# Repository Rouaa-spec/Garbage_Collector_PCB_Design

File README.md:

# [Hardware Design] Carte Électronique de Contrôle — Robot Autonome Tri-Canettes

Ce dépôt rassemble les fichiers de conception matérielle de la carte de contrôle dédiée à un robot autonome de collecte et de tri de déchets. 

La carte centralise la gestion de l'alimentation (Li-Ion), le pilotage des moteurs DC et l'acquisition des capteurs de navigation sur bus partagés.

📌 **Statut du projet :** 
* 🟧 **Routage PCB (KiCad) :** En cours de réalisation...

---

## 🗺️ Architecture Système 

Le schéma architectural conçu pour la carte :

---

## 🛠️ Spécifications & Choix des Composants

### 1. Unité de Traitement & Logique (MCU)
* **Microcontrôleur :** **STM32G431RBT6** (Cortex-M4, 170 MHz). Sélectionné pour ses timers avancés (gestion des moteurs et servo) et sa large connectivité matérielle.

### 2. Gestion de l'Énergie (Power Management)
* **Contrôleur de Charge :** **bq25896RTWR** (Switching Charger). Assure la charge rapide de la batterie Lithium-Ion via USB-C et la gestion dynamique du chemin de puissance (Power Path).
* **Jauge de Batterie :** **bq27220** (Fuel Gauge). Suivi précis de l'état de charge (SoC) via le bus I²C2.
* **Régulation :** LDO **AP2112K-3.3** (600mA) pour l'alimentation stable de la section logique et des capteurs.

### 3. Contrôle des Actionneurs (Motor Drive)
* **Driver Moteurs :** **DRV8833** (Double Pont en H) pour le pilotage de 2 motoréducteurs CC (CH-N20-3) via signaux PWM (`TIM1` et `TIM3`).
* **Servomoteur :** Sortie dédiée pour un **Servo MG90S** (Pince de préhension) piloté par le timer `TIM15`.

### 4. Acquisition Capteurs (Sensors)
Répartition sur trois bus physiques I²C indépendants pour éviter la saturation et les conflits d'adresses :
* **Bus I²C1 :** Centrale inertielle IMU **MPU-6050** (Odométrie).
* **Bus I²C2 :** Section Power Management (**bq27220** et **bq25896**).
* **Bus I²C3 :** Télémètres Laser ToF **VL53L0X** (Évitement d'obstacles) et capteur de couleur/proximité **APDS9960** (Tri des canettes). 
  * *Note de conception :* Les broches `XSHUT` des VL53L0X sont routées vers des GPIOs du STM32 pour configurer leurs adresses de manière logicielle et séquentielle.

---

## 📄 Dossier de Conception (Schématiques)

### Étage Microcontrôleur (MCU)

### Gestion d'Énergie (Power Management)

### Bloc Capteurs (Sensors)

### Commande Moteurs (Motor Drive)

---

## 📂 Organisation du Dépôt

```text
├── 📂 Hardware/               # Fichiers sources CAO KiCad (.kicad_sch, .kicad_pcb en cours)
├── 📂 Documents/              
│   ├── 📄 Schematic_Print.pdf # Schématique complet 
└── 📄 README.md
```

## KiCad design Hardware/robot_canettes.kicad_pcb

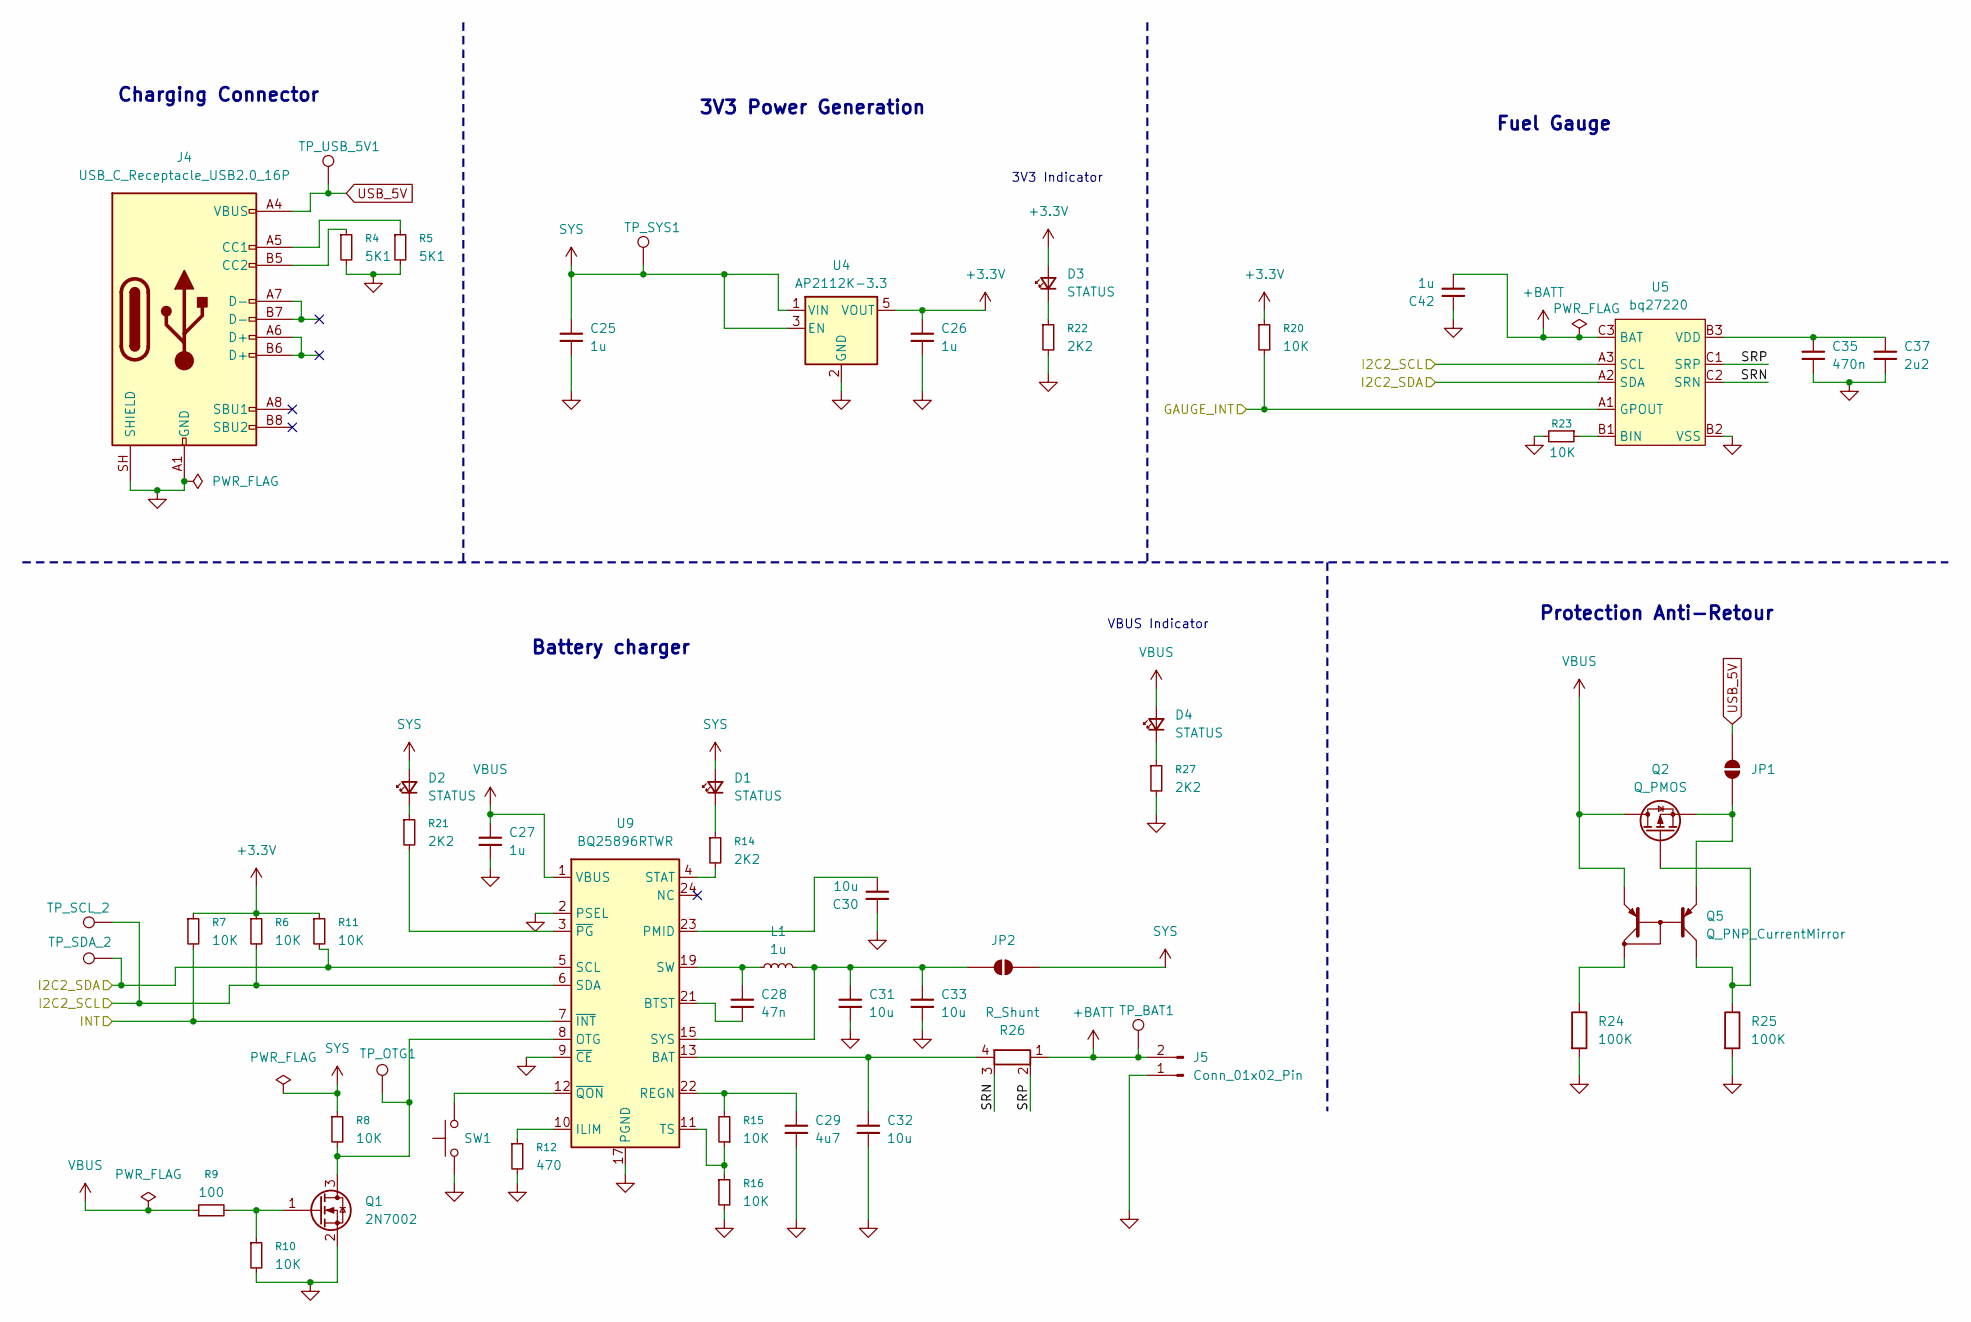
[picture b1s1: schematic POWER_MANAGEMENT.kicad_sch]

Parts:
C25, C26, C27, C42: 1u; C_0402_1005Metric; JLCPCB Part # C52923
C28: 47n; C_0402_1005Metric; JLCPCB Part # C5254486
C29: 4u7; C_0402_1005Metric; JLCPCB Part # C368809
C30, C31, C32, C33: 10u; C_0603_1608Metric; JLCPCB Part # C19702
C35: 470n; C_0402_1005Metric; JLCPCB Part # C2443202
C37: 2u2; C_0402_1005Metric; JLCPCB Part # C107370
D1: STATUS; LED_0603_1608Metric; JLCPCB Part # C2287
D2, D3, D4: STATUS; LED_0603_1608Metric; JLCPCB Part # C72043
J4: USB_C_Receptacle_USB2.0_16P; USB_C_Receptacle_GCT_USB4105-xx-A_16P_TopMnt_Horizontal; JLCPCB Part # C2765186
J5: Conn_01x02_Pin; JST_PH_B2B-PH-K_1x02_P2.00mm_Vertical
JP1, JP2: SolderJumper-2_P1.3mm_Open_Pad1.0x1.5mm
L1: 1u; L_APV_ANR4010; JLCPCB Part # C354578
Q1: 2N7002; SOT-23; JLCPCB Part # C8485
Q2: Q_PMOS; SOT-23; JLCPCB Part # C177033
Q5: Q_PNP_CurrentMirror; SOT-363_SC-70-6; JLCPCB Part # C42387345
R4, R5: 5K1; R_0402_1005Metric; JLCPCB Part # C25905
R6, R7, R8, R10, R11, R15, R16, R20, R23: 10K; R_0402_1005Metric; JLCPCB Part # C844714
R9: 100; R_0402_1005Metric; JLCPCB Part # C25076
R12: 470; R_0402_1005Metric; JLCPCB Part # C25117
R14, R21, R22, R27: 2K2; R_0402_1005Metric; JLCPCB Part # C25879
R24, R25: 100K; R_0603_1608Metric; JLCPCB Part # C25803
R26: R_Shunt; R_Shunt_Ohmite_LVK12; JLCPCB Part # C500740
SW1: SW_SPST_Omron_B3FS-101xP; JLCPCB Part # C271753
TP_BAT1: TestPoint_Pad_D1.5mm
TP_OTG1: TestPoint_Pad_D1.5mm
TP_SCL_2: TestPoint_Pad_D1.5mm
TP_SDA_2: TestPoint_Pad_D1.5mm
TP_SYS1: TestPoint_Pad_D1.5mm
TP_USB_5V1: TestPoint_Pad_D1.5mm
U4: AP2112K-3.3; SOT-23-5; JLCPCB Part # C51118
U5: bq27220; BGA-9_3x3_1.62x1.58mm_Pitch0.5mm; JLCPCB Part # C528617
U9: BQ25896RTWR; Texas_RTW_WQFN-24-1EP_4x4mm_P0.5mm_EP2.7x2.7mm_ThermalVias; JLCPCB Part # C181475

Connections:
+3.3V: C26.1, D3.2 (A), R6.1, R7.1, R11.1, R20.1, U4.5 (VOUT); also elsewhere on the board
+BATT: C42.2, J5.2, R26.1, TP_BAT1.1 (1_1), U5.C3 (BAT)
/MCU/GAUGE_INT: R20.2, U5.A1 (GPOUT); also elsewhere on the board
/MCU/I2C2_SCL: R6.2, TP_SCL_2.1 (1_1), U5.A3 (SCL), U9.6 (SDA); also elsewhere on the board
/MCU/I2C2_SDA: R11.2, TP_SDA_2.1 (1_1), U5.A2 (SDA), U9.5 (SCL); also elsewhere on the board
/MCU/INT: R7.2, U9.7 (~INT); also elsewhere on the board
/POWER_MANAGEMENT/SRN: R26.3, U5.C2 (SRN)
/POWER_MANAGEMENT/SRP: R26.2, U5.C1 (SRP)
unnamed: C28.1, L1.1, U9.19 (SW), U9.20 (SW)
unnamed: C32.1, R26.4, U9.13 (BAT), U9.14 (BAT)
unnamed: D1.1 (K), R14.1
unnamed: D2.1 (K), R21.1
unnamed: D3.1 (K), R22.1
unnamed: D4.1 (K), R27.1
unnamed: J4.A5 (CC1), R5.1
unnamed: J4.B5 (CC2), R4.1
unnamed: JP1.1 (A), Q2.2 (S), Q5.1 (E1)
unnamed: C31.1, C33.1, JP2.2 (B), L1.2, U9.15 (SYS), U9.16 (SYS)
unnamed: Q1.3 (D), R8.2, TP_OTG1.1 (1_1), U9.8 (OTG)
unnamed: Q1.1 (G), R9.2, R10.1
unnamed: Q2.1 (G), Q5.6 (C1), R25.1
unnamed: Q5.3 (C2), R24.1
unnamed: R23.1, U5.B1 (BIN)
unnamed: C35.1, C37.1, U5.B3 (VDD)
unnamed: C28.2, U9.21 (BTST)
unnamed: R12.1, U9.10 (ILIM)
unnamed: C30.2, U9.23 (PMID)
unnamed: C29.1, R15.2, U9.22 (REGN)
unnamed: R14.2, U9.4 (STAT)
unnamed: R15.1, R16.1, U9.11 (TS)
unnamed: R21.2, U9.3 (~PG)
unnamed: SW1.2, U9.12 (~QON)
SYS: C25.1, D1.2 (A), D2.2 (A), JP2.1 (A), R8.1, TP_SYS1.1 (1_1), U4.1 (VIN), U4.3 (EN)
USB_5V: J4.A4 (VBUS), J4.A9 (VBUS), J4.B4 (VBUS), J4.B9 (VBUS), JP1.2 (B), TP_USB_5V1.1 (1_1)
VBUS: C27.1, D4.2 (A), Q2.3 (D), Q5.4 (E2), R9.1, U9.1 (VBUS); also elsewhere on the board

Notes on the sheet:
Battery charger
Charging Connector
3V3 Indicator
Fuel Gauge
3V3 Power Generation
Protection Anti-Retour
VBUS Indicator

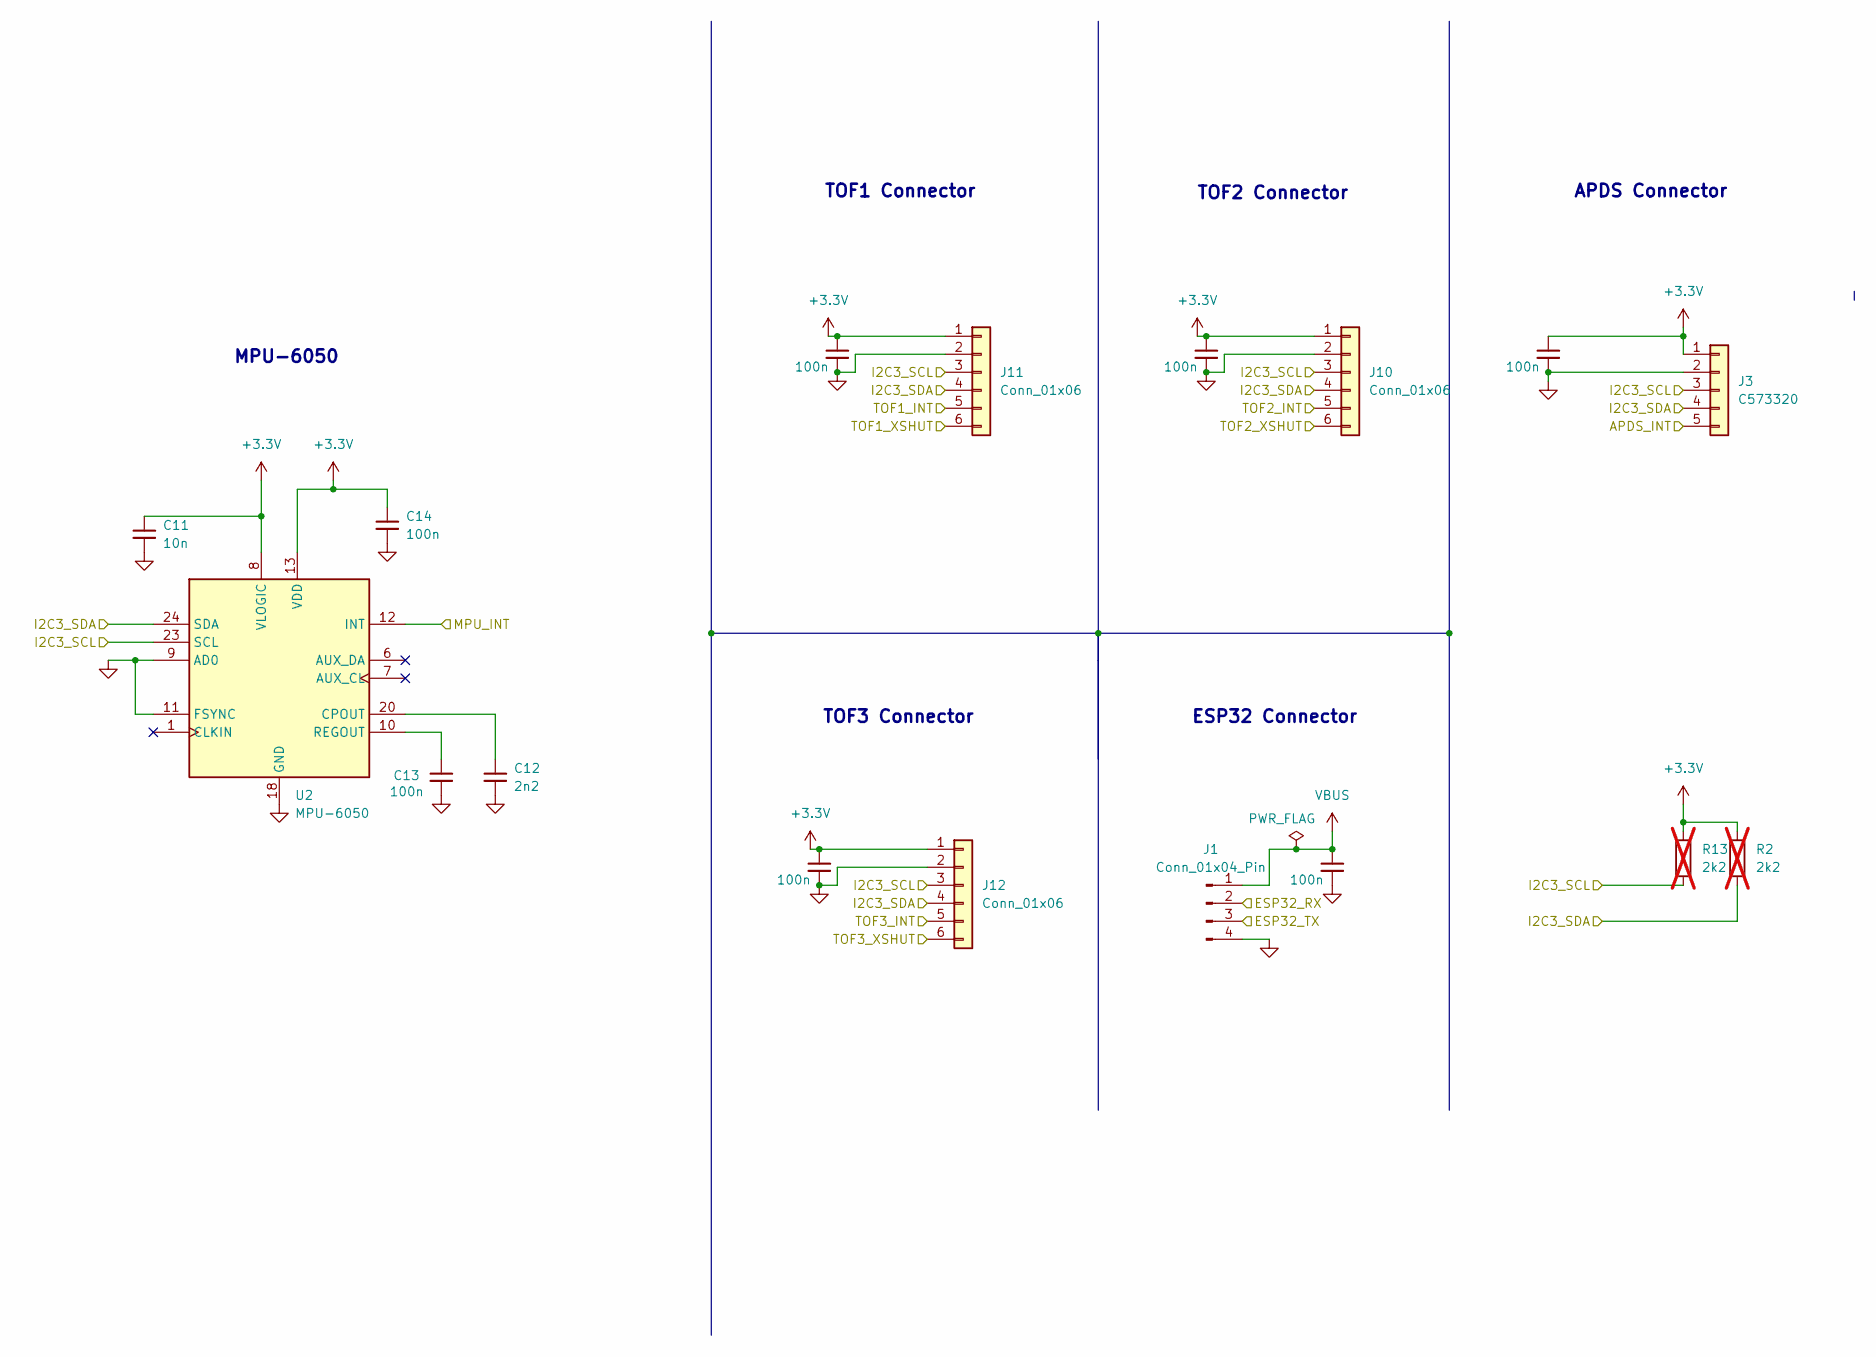
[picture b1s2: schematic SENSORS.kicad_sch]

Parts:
C11: 10n; C_0402_1005Metric; JLCPCB PART # C15195
C12: 2n2; C_0402_1005Metric; JLCPCB PART # C1531
C13, C14, C38, C39, C40, C41, C43: 100n; C_0402_1005Metric; JLCPCB PART # C1525
J1: Conn_01x04_Pin; JST_PH_B4B-PH-K_1x04_P2.00mm_Vertical
J3: C573320; JST_PH_B5B-PH-K_1x05_P2.00mm_Vertical; JLCPCB PART# C573320
J10, J11, J12: Conn_01x06; JST_PH_B6B-PH-K_1x06_P2.00mm_Vertical
R2, R13: 2k2; R_0402_1005Metric; JLCPCB PART # C174143; not fitted
U2: MPU-6050; InvenSense_QFN-24_4x4mm_P0.5mm; JLCPCB PART # C24112

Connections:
+3.3V: C11.1, C14.1, C38.1, C39.1, C40.1, C41.1, J3.1, J10.1, J11.1, J12.1, R2.1, R13.1, U2.8 (VLOGIC), U2.13 (VDD); also elsewhere on the board
/MCU/APDS_INT: J3.5; also elsewhere on the board
/MCU/ESP32_RX: J1.3; also elsewhere on the board
/MCU/ESP32_TX: J1.2; also elsewhere on the board
/MCU/I2C3_SCL: J3.3, J10.3, J11.3, J12.3, R13.2, U2.23 (SCL); also elsewhere on the board
/MCU/I2C3_SDA: J3.4, J10.4, J11.4, J12.4, R2.2, U2.24 (SDA); also elsewhere on the board
/MCU/MPU_INT: U2.12 (INT); also elsewhere on the board
/MCU/TOF1_INT: J12.5; also elsewhere on the board
/MCU/TOF1_XSHUT: J12.6; also elsewhere on the board
/MCU/TOF2_INT: J10.5; also elsewhere on the board
/MCU/TOF2_XSHUT: J10.6; also elsewhere on the board
/MCU/TOF3_INT: J11.5; also elsewhere on the board
/MCU/TOF3_XSHUT: J11.6; also elsewhere on the board
unnamed: C12.1, U2.20 (CPOUT)
unnamed: C13.1, U2.10 (REGOUT)
VBUS: C43.1, J1.1; also elsewhere on the board

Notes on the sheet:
TOF1 Connector
APDS Connector
ESP32 Connector
TOF2 Connector
MPU-6050
TOF3 Connector

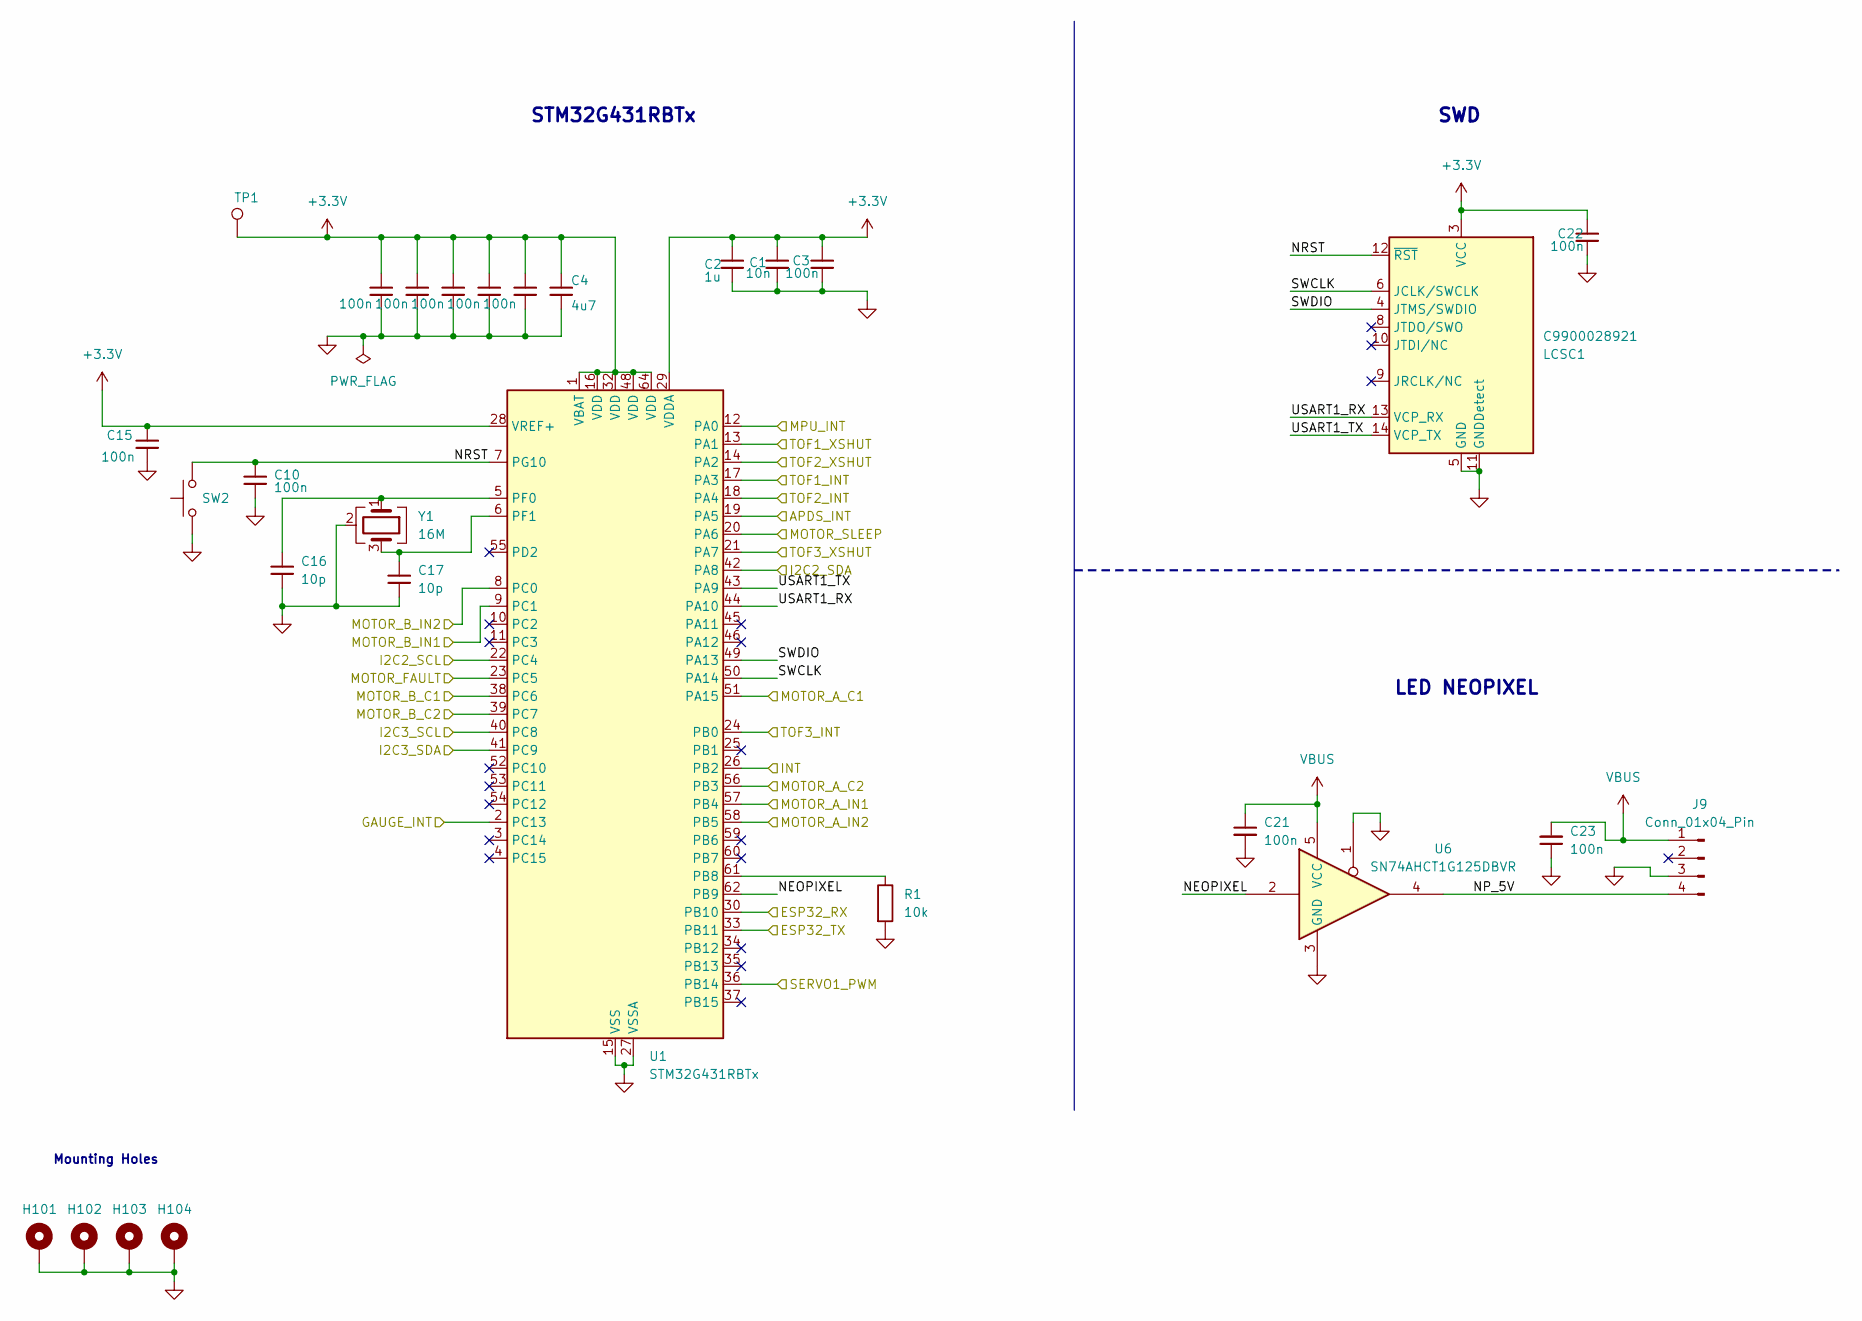
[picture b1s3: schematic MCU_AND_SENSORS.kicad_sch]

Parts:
C1: 10n; C_0402_1005Metric; JLCPCB PART# C15195
C2: 1u; C_0603_1608Metric; JLCPCB PART # C141772
C3, C6, C7, C8, C9, C10, C15, C22: 100n; C_0402_1005Metric; JLCPCB PART # C1525
C4: 4u7; C_0603_1608Metric
C5: 100n; C_0402_1005Metric
C16, C17: 10p; C_0603_1608Metric; JLCPCB PART # C123155
C21, C23: 100n; C_0402_1005Metric; JLCPCB Part # C1525
H101, H102, H103, H104: MountingHole_Pad; MountingHole_3.2mm_M3_Pad_Via
J9: Conn_01x04_Pin; JST_PH_B4B-PH-K_1x04_P2.00mm_Vertical; JLCPCB Part # C2691448
LCSC1: C9900028921; PinHeader_2x07_P1.27mm_Vertical_SMD; JLCPCB PART # C9900028921
R1: 10k; R_0402_1005Metric; JLCPCB PART # C174175
SW2: SW_SPST_Omron_B3FS-101xP; JLCPCB Part # C271753
TP1: TestPoint; TestPoint_Pad_D1.5mm
U1: STM32G431RBTx; LQFP-64_10x10mm_P0.5mm; JLCPCB PART # C431633
U6: SN74AHCT1G125DBVR; SOT-23-5; JLCPCB Part # C20617903
Y1: 16M; Crystal_SMD_EuroQuartz_MT-4Pin_3.2x2.5mm; JLCPCB PART # C13738

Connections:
+3.3V: C1.1, C2.1, C3.1, C4.1, C5.1, C6.1, C7.1, C8.1, C9.1, C15.1, C22.1, LCSC1.3 (VCC), TP1.1 (1_1), U1.1 (VBAT), U1.16 (VDD), U1.28 (VREF+), U1.29 (VDDA), U1.32 (VDD), U1.48 (VDD), U1.64 (VDD); also elsewhere on the board
/MCU/APDS_INT: U1.19 (PA5); also elsewhere on the board
/MCU/ESP32_RX: U1.30 (PB10); also elsewhere on the board
/MCU/ESP32_TX: U1.33 (PB11); also elsewhere on the board
/MCU/GAUGE_INT: U1.2 (PC13); also elsewhere on the board
/MCU/I2C2_SCL: U1.22 (PC4); also elsewhere on the board
/MCU/I2C2_SDA: U1.42 (PA8); also elsewhere on the board
/MCU/I2C3_SCL: U1.40 (PC8); also elsewhere on the board
/MCU/I2C3_SDA: U1.41 (PC9); also elsewhere on the board
/MCU/INT: U1.26 (PB2); also elsewhere on the board
/MCU/MOTOR_A_C1: U1.51 (PA15); also elsewhere on the board
/MCU/MOTOR_A_C2: U1.56 (PB3); also elsewhere on the board
/MCU/MOTOR_A_IN1: U1.57 (PB4); also elsewhere on the board
/MCU/MOTOR_A_IN2: U1.58 (PB5); also elsewhere on the board
/MCU/MOTOR_B_C1: U1.38 (PC6); also elsewhere on the board
/MCU/MOTOR_B_C2: U1.39 (PC7); also elsewhere on the board
/MCU/MOTOR_B_IN1: U1.9 (PC1); also elsewhere on the board
/MCU/MOTOR_B_IN2: U1.8 (PC0); also elsewhere on the board
/MCU/MOTOR_FAULT: U1.23 (PC5); also elsewhere on the board
/MCU/MOTOR_SLEEP: U1.20 (PA6); also elsewhere on the board
/MCU/MPU_INT: U1.12 (PA0); also elsewhere on the board
/MCU/NEOPIXEL: U1.62 (PB9), U6.2
/MCU/NP_5V: J9.4, U6.4
/MCU/NRST: C10.1, LCSC1.12 (~RST), SW2.2, U1.7 (PG10)
/MCU/SERVO1_PWM: U1.36 (PB14); also elsewhere on the board
/MCU/SWCLK: LCSC1.6 (JCLK/SWCLK), U1.50 (PA14)
/MCU/SWDIO: LCSC1.4 (JTMS/SWDIO), U1.49 (PA13)
/MCU/TOF1_INT: U1.17 (PA3); also elsewhere on the board
/MCU/TOF1_XSHUT: U1.13 (PA1); also elsewhere on the board
/MCU/TOF2_INT: U1.18 (PA4); also elsewhere on the board
/MCU/TOF2_XSHUT: U1.14 (PA2); also elsewhere on the board
/MCU/TOF3_INT: U1.24 (PB0); also elsewhere on the board
/MCU/TOF3_XSHUT: U1.21 (PA7); also elsewhere on the board
/MCU/USART1_RX: LCSC1.13 (VCP_RX), U1.44 (PA10)
/MCU/USART1_TX: LCSC1.14 (VCP_TX), U1.43 (PA9)
unnamed: R1.1, U1.61 (PB8)
unnamed: C16.1, U1.5 (PF0), Y1.1
unnamed: C17.1, U1.6 (PF1), Y1.3
VBUS: C21.1, C23.2, J9.1, U6.5 (VCC); also elsewhere on the board

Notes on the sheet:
LED NEOPIXEL
SWD
Mounting Holes
STM32G431RBTx

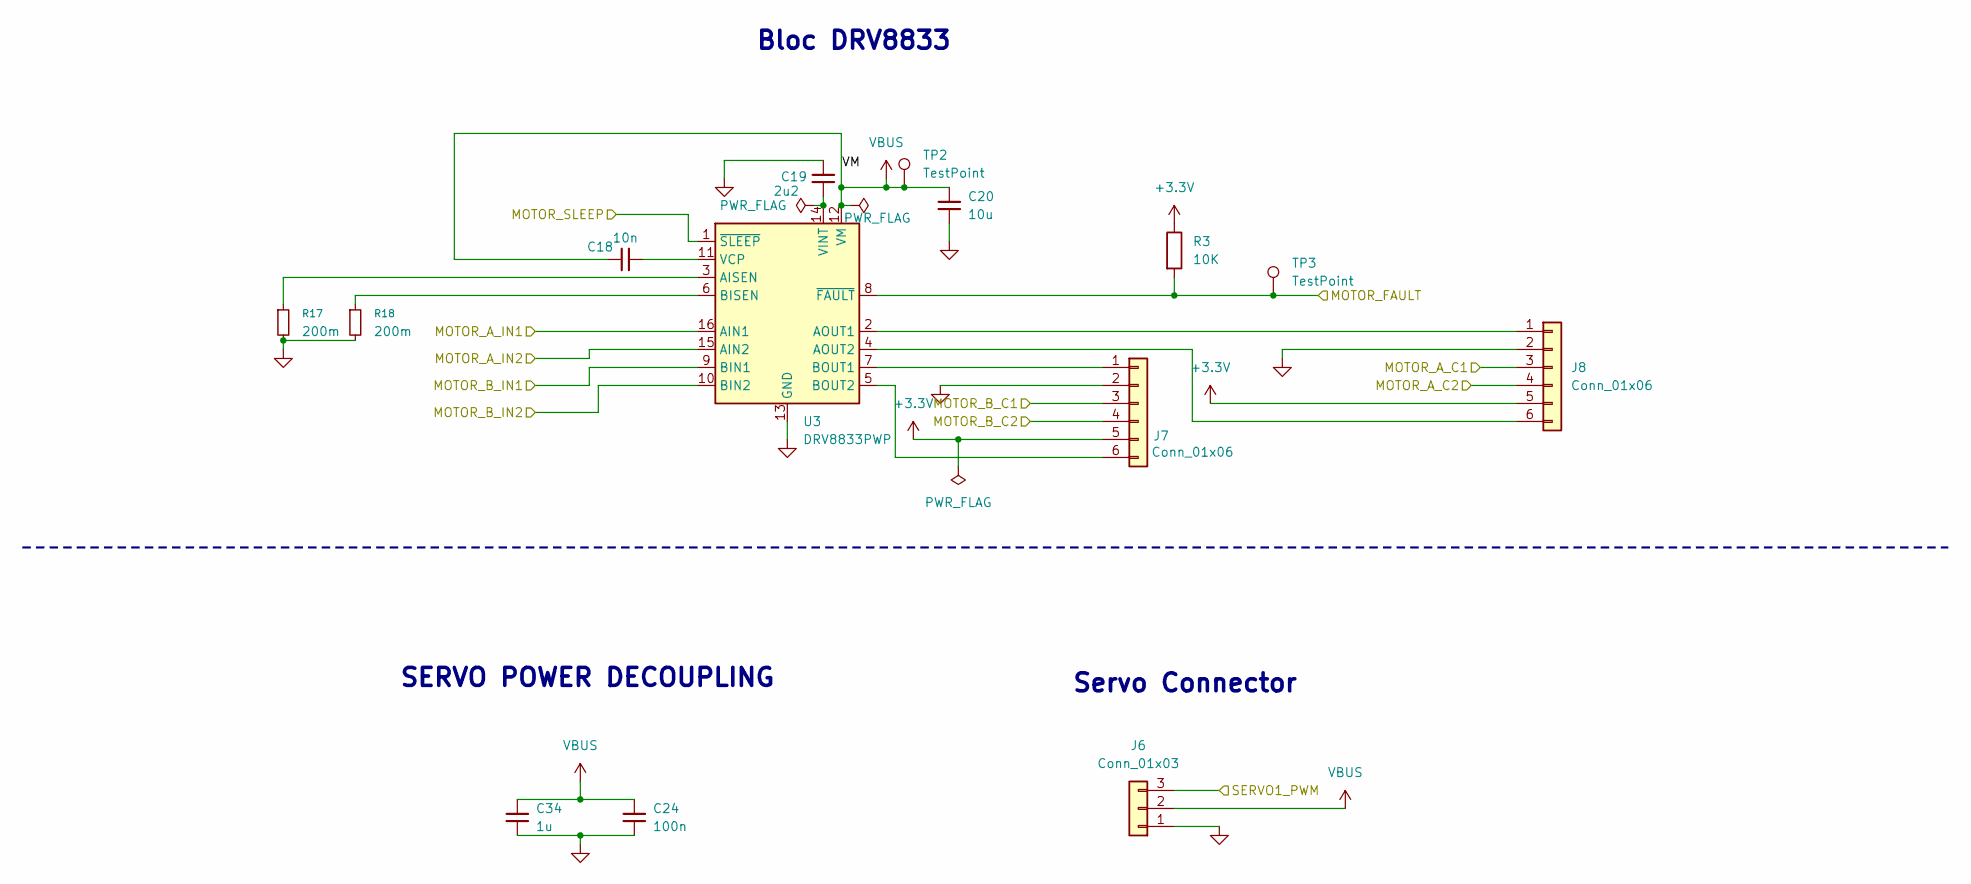
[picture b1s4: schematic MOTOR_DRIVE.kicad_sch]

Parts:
C18: 10n; C_0402_1005Metric; JLCPCB Part # C15195
C19: 2u2; C_0402_1005Metric; JLCPCB Part # C12530
C20: 10u; C_0805_2012Metric; JLCPCB Part # C380332
C24: 100n; C_0402_1005Metric; JLCPCB Part # C1525
C34: 1u; C_0402_1005Metric
J6: Conn_01x03; JST_PH_B3B-PH-K_1x03_P2.00mm_Vertical; JLCPCB Part # C49257
J7, J8: Conn_01x06; JST_PH_B6B-PH-K_1x06_P2.00mm_Vertical; JLCPCB Part # C265069
R3: 10K; R_0402_1005Metric; JLCPCB Part # C844714
R17, R18: 200m; R_1206_3216Metric; JLCPCB PART # C1727756
TP2, TP3: TestPoint; TestPoint_Pad_D1.5mm
U3: DRV8833PWP; HTSSOP-16-1EP_4.4x5mm_P0.65mm_EP3.4x5mm_Mask2.46x2.31mm; JLCPCB Part # C50506

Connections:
+3.3V: J7.5, J8.5, R3.1; also elsewhere on the board
/MCU/MOTOR_A_C1: J8.3; also elsewhere on the board
/MCU/MOTOR_A_C2: J8.4; also elsewhere on the board
/MCU/MOTOR_A_IN1: U3.16 (AIN1); also elsewhere on the board
/MCU/MOTOR_A_IN2: U3.15 (AIN2); also elsewhere on the board
/MCU/MOTOR_B_C1: J7.3; also elsewhere on the board
/MCU/MOTOR_B_C2: J7.4; also elsewhere on the board
/MCU/MOTOR_B_IN1: U3.9 (BIN1); also elsewhere on the board
/MCU/MOTOR_B_IN2: U3.10 (BIN2); also elsewhere on the board
/MCU/MOTOR_FAULT: R3.2, TP3.1 (1_1), U3.8 (~FAULT); also elsewhere on the board
/MCU/MOTOR_SLEEP: U3.1 (~SLEEP); also elsewhere on the board
/MCU/SERVO1_PWM: J6.3; also elsewhere on the board
unnamed: J7.1, U3.7 (BOUT1)
unnamed: J7.6, U3.5 (BOUT2)
unnamed: J8.1, U3.2 (AOUT1)
unnamed: J8.6, U3.4 (AOUT2)
unnamed: R17.1, U3.3 (AISEN)
unnamed: R18.1, U3.6 (BISEN)
unnamed: C18.2, U3.11 (VCP)
unnamed: C19.2, U3.14 (VINT)
VBUS: C18.1, C20.1, C24.1, C34.1, J6.2, TP2.1 (1_1), U3.12 (VM); also elsewhere on the board

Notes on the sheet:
Servo Connector
SERVO POWER DECOUPLING
Bloc DRV8833

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
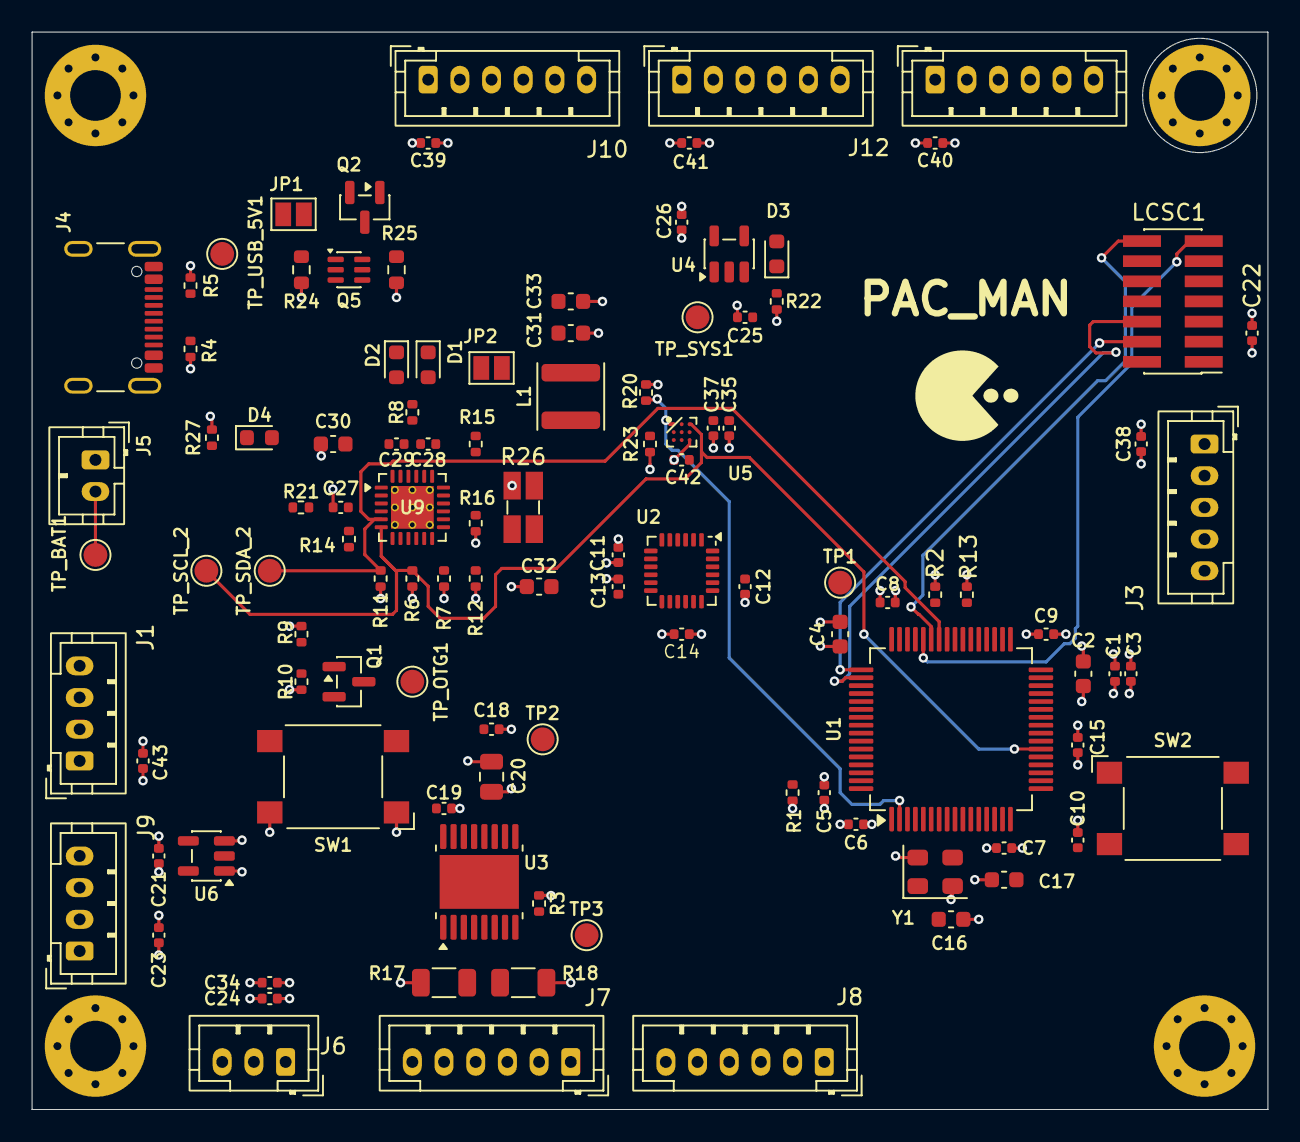
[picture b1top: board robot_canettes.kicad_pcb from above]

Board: 4 copper layers, 78.0 x 68.0 mm, 113 parts (0 on the bottom side), 79 nets.
